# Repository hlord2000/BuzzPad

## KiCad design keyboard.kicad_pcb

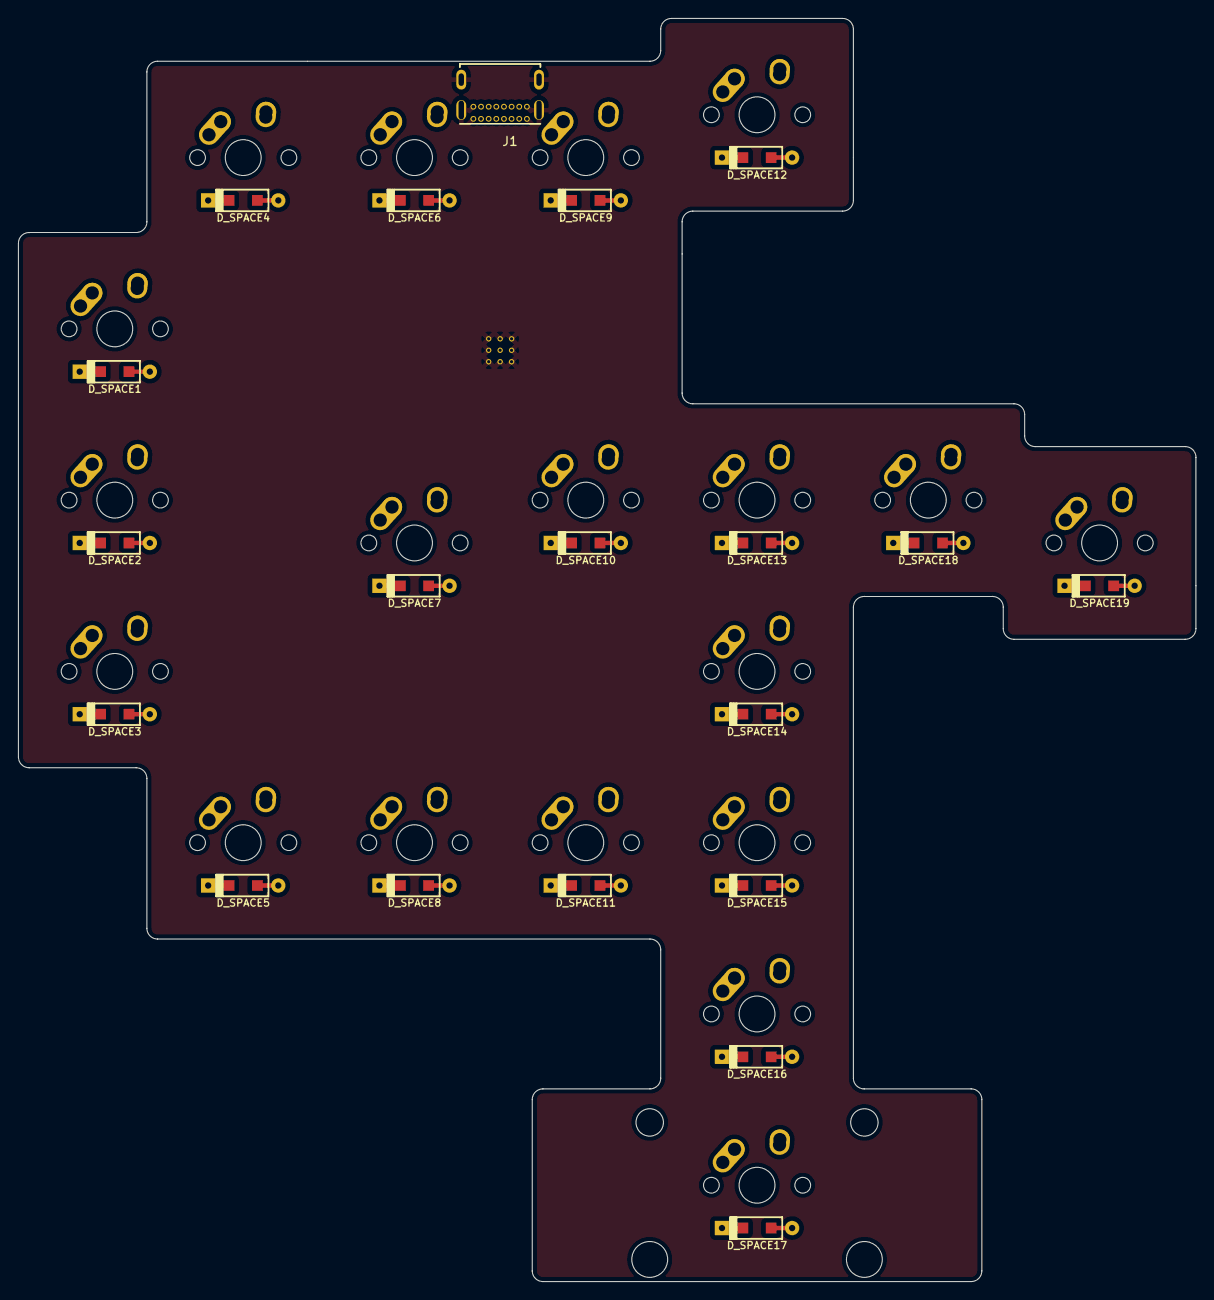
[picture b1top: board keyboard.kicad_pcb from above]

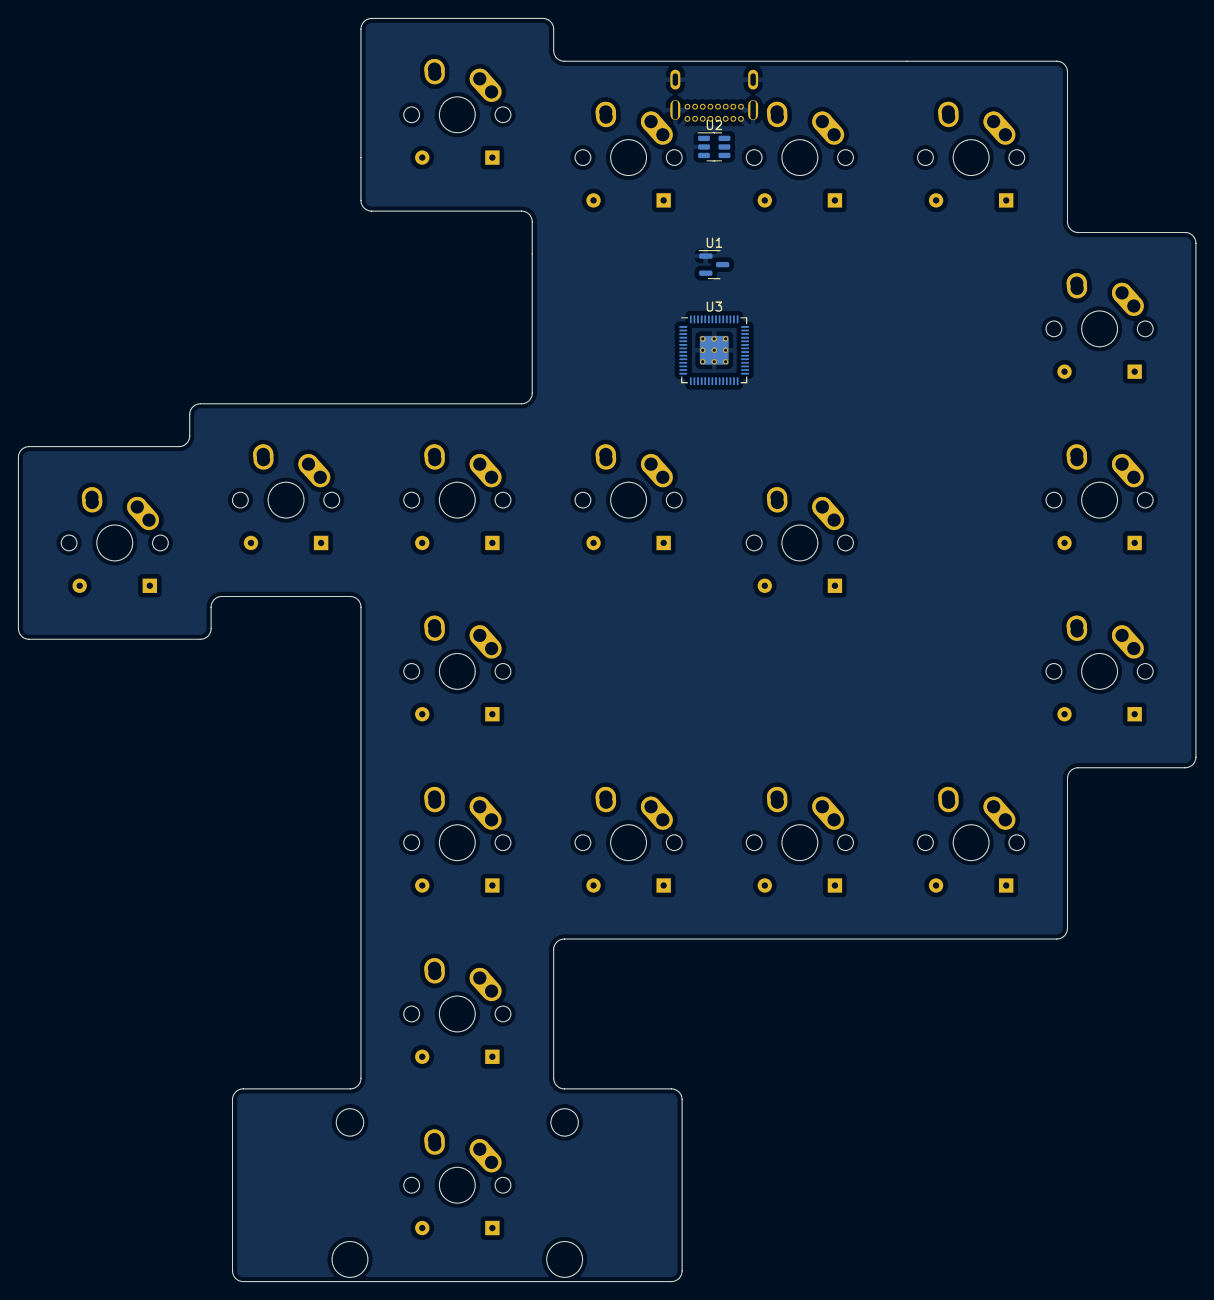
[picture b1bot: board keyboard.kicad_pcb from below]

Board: 2 copper layers, 131.0 x 140.5 mm, 42 parts (3 on the bottom side), 38 nets.

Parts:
D_SPACE1, D_SPACE2, D_SPACE3, D_SPACE4, D_SPACE5, D_SPACE6, D_SPACE7, D_SPACE8, D_SPACE9, D_SPACE10, D_SPACE11, D_SPACE12, D_SPACE13, D_SPACE14, D_SPACE15, D_SPACE16, D_SPACE17, D_SPACE18, D_SPACE19: D; D_SOD123_axial
J1: USB4085-GF-A_REVA4; GCT_USB4085-GF-A_REVA4
K_SPACE1, K_SPACE2, K_SPACE3, K_SPACE4, K_SPACE5, K_SPACE6, K_SPACE7, K_SPACE8, K_SPACE9, K_SPACE10, K_SPACE11, K_SPACE12, K_SPACE13, K_SPACE14, K_SPACE15, K_SPACE16, K_SPACE18, K_SPACE19: KEYSW; MX-1U-NoLED
K_SPACE17: KEYSW; MX-2.5U-NoLED
U1: XC6206P332MR; SOT-23
U2: SRV05-4; SOT-23-6
U3: RP2040; RP2040-QFN-56

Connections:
+3V3: U1.2 (VO), U3.1 (IOVDD), U3.10 (IOVDD), U3.22 (IOVDD), U3.33 (IOVDD), U3.42 (IOVDD), U3.43 (ADC_AVDD), U3.44 (VREG_IN), U3.48 (USB_VDD), U3.49 (IOVDD)
+5V: J1.A4 (VBUS), J1.A9 (VBUS), J1.B4 (VBUS), J1.B9 (VBUS), U1.3 (VI), U2.5 (VP)
/DN1: J1.A7 (DN1), J1.B7 (DN2), U2.4 (IO3), U2.6 (IO4)
/DP1: J1.A6 (DP1), J1.B6 (DP2), U2.1 (IO1), U2.3 (IO2)
GND: J1.A1 (GND), J1.A12 (GND), J1.B1 (GND), J1.B12 (GND), J1.P1 (SHELL), J1.P2 (SHELL), J1.P3 (SHELL), J1.P4 (SHELL), U1.1 (GND), U2.2 (VN), U3.19 (TESTEN), U3.57 (GND)
unnamed: D_SPACE1.2 (A), K_SPACE1.2
unnamed: D_SPACE2.2 (A), K_SPACE2.2
unnamed: D_SPACE3.2 (A), K_SPACE3.2
unnamed: D_SPACE4.2 (A), K_SPACE4.2
unnamed: D_SPACE5.2 (A), K_SPACE5.2
unnamed: D_SPACE6.2 (A), K_SPACE6.2
unnamed: D_SPACE7.2 (A), K_SPACE7.2
unnamed: D_SPACE8.2 (A), K_SPACE8.2
unnamed: D_SPACE9.2 (A), K_SPACE9.2
unnamed: D_SPACE10.2 (A), K_SPACE10.2
unnamed: D_SPACE11.2 (A), K_SPACE11.2
unnamed: D_SPACE12.2 (A), K_SPACE12.2
unnamed: D_SPACE13.2 (A), K_SPACE13.2
unnamed: D_SPACE14.2 (A), K_SPACE14.2
unnamed: D_SPACE15.2 (A), K_SPACE15.2
unnamed: D_SPACE16.2 (A), K_SPACE16.2
unnamed: D_SPACE17.2 (A), K_SPACE17.2
unnamed: D_SPACE18.2 (A), K_SPACE18.2
unnamed: D_SPACE19.2 (A), K_SPACE19.2
unnamed: U3.23 (DVDD), U3.45 (VREG_VOUT), U3.50 (DVDD)
col0: K_SPACE1.1, K_SPACE2.1, K_SPACE3.1, U3.8 (GPIO6)
col1: K_SPACE4.1, K_SPACE5.1, U3.9 (GPIO7)
col2: K_SPACE6.1, K_SPACE7.1, K_SPACE8.1, U3.11 (GPIO8)
col3: K_SPACE9.1, K_SPACE10.1, K_SPACE11.1, U3.12 (GPIO9)
col4: K_SPACE12.1, K_SPACE13.1, K_SPACE14.1, K_SPACE15.1, K_SPACE16.1, K_SPACE17.1, U3.13 (GPIO10)
col5: K_SPACE18.1, U3.14 (GPIO11)
col6: K_SPACE19.1, U3.15 (GPIO12)
row0: D_SPACE1.1 (K), D_SPACE4.1 (K), D_SPACE6.1 (K), D_SPACE9.1 (K), D_SPACE12.1 (K), U3.2 (GPIO0)
row1: D_SPACE2.1 (K), D_SPACE7.1 (K), D_SPACE10.1 (K), D_SPACE13.1 (K), D_SPACE18.1 (K), D_SPACE19.1 (K), U3.3 (GPIO1)
row2: D_SPACE3.1 (K), D_SPACE5.1 (K), D_SPACE8.1 (K), D_SPACE11.1 (K), D_SPACE14.1 (K), U3.4 (GPIO2)
row3: D_SPACE15.1 (K), U3.5 (GPIO3)
row4: D_SPACE16.1 (K), U3.6 (GPIO4)
row5: D_SPACE17.1 (K), U3.7 (GPIO5)

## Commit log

2022-02-15 Initial commit.
2022-02-15 Image.
2022-02-15 Layout file from KBLE.
2022-02-23 AHHHHHHHHHHHHHHHHHH
2022-02-27 RP2040 rework
2022-03-07 Changes to keyboard schematic--added QSPI flash. TODO: add decoupling caps.
